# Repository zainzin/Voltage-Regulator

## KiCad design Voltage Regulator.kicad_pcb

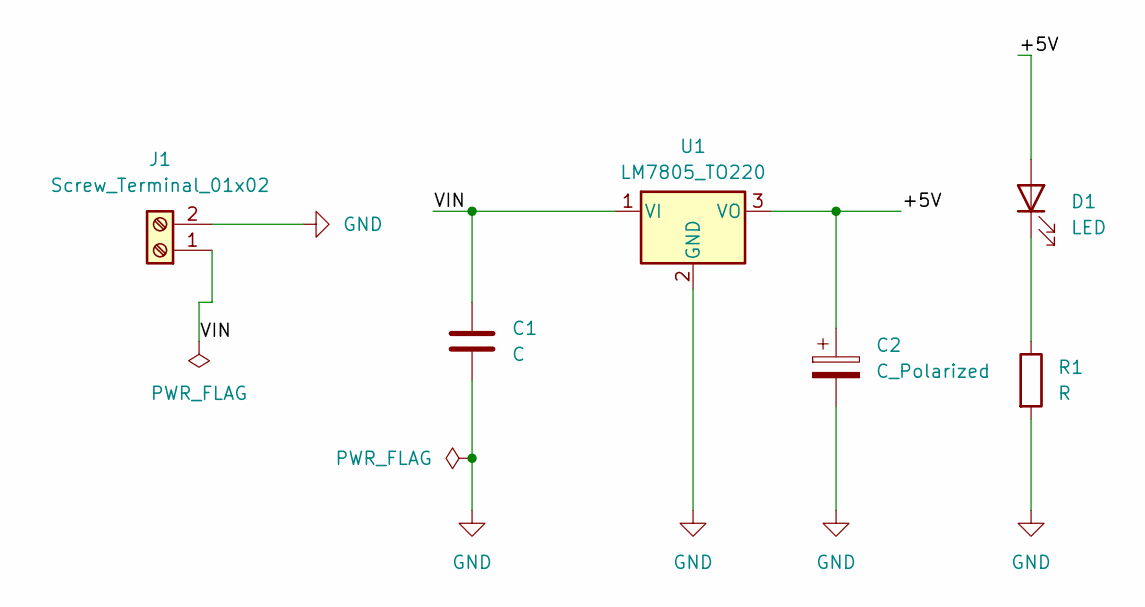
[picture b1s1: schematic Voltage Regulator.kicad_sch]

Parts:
C1: C; C_Disc_D5.0mm_W2.5mm_P5.00mm
C2: C_Polarized; CP_Radial_D6.3mm_P2.50mm
D1: LED; LED_D5.0mm
J1: Screw_Terminal_01x02; TerminalBlock_Phoenix_PT-1,5-2-5.0-H_1x02_P5.00mm_Horizontal
R1: R; R_Axial_DIN0207_L6.3mm_D2.5mm_P10.16mm_Horizontal
U1: LM7805_TO220; TO-220-3_Vertical

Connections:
/+5V: C2.1, D1.2 (A), U1.3 (VO)
/VIN: C1.1, J1.1, U1.1 (VI)
GND: C1.2, C2.2, J1.2, R1.2, U1.2 (GND)
unnamed: D1.1 (K), R1.1

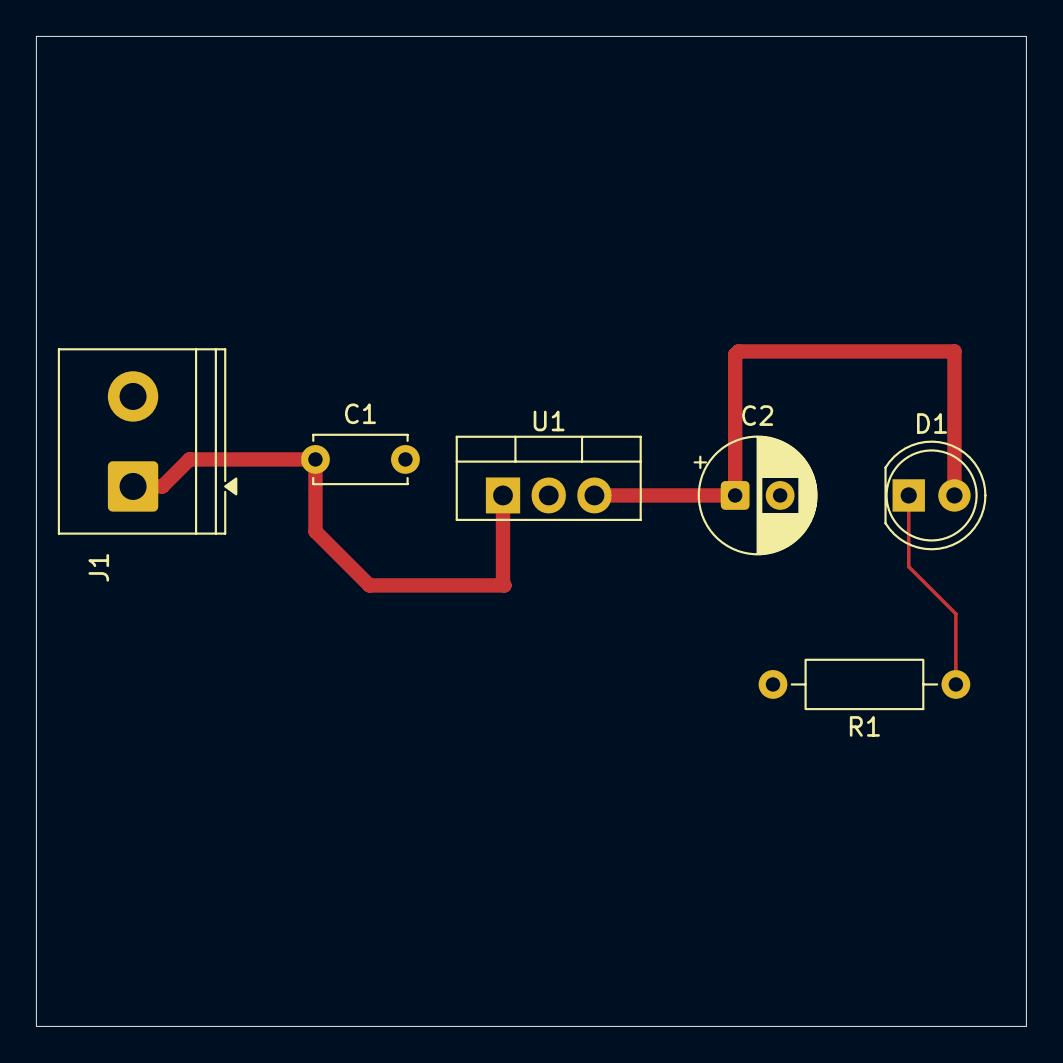
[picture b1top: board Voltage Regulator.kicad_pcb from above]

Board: 2 copper layers, 55.0 x 55.0 mm, 6 parts (0 on the bottom side), 4 nets.
